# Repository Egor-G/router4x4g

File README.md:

4x M.2 LTE modems router project.
Based on Myirtech MYC-Y6ULX SoM.
Supply volatage 12-24V.
Openwrt OS.

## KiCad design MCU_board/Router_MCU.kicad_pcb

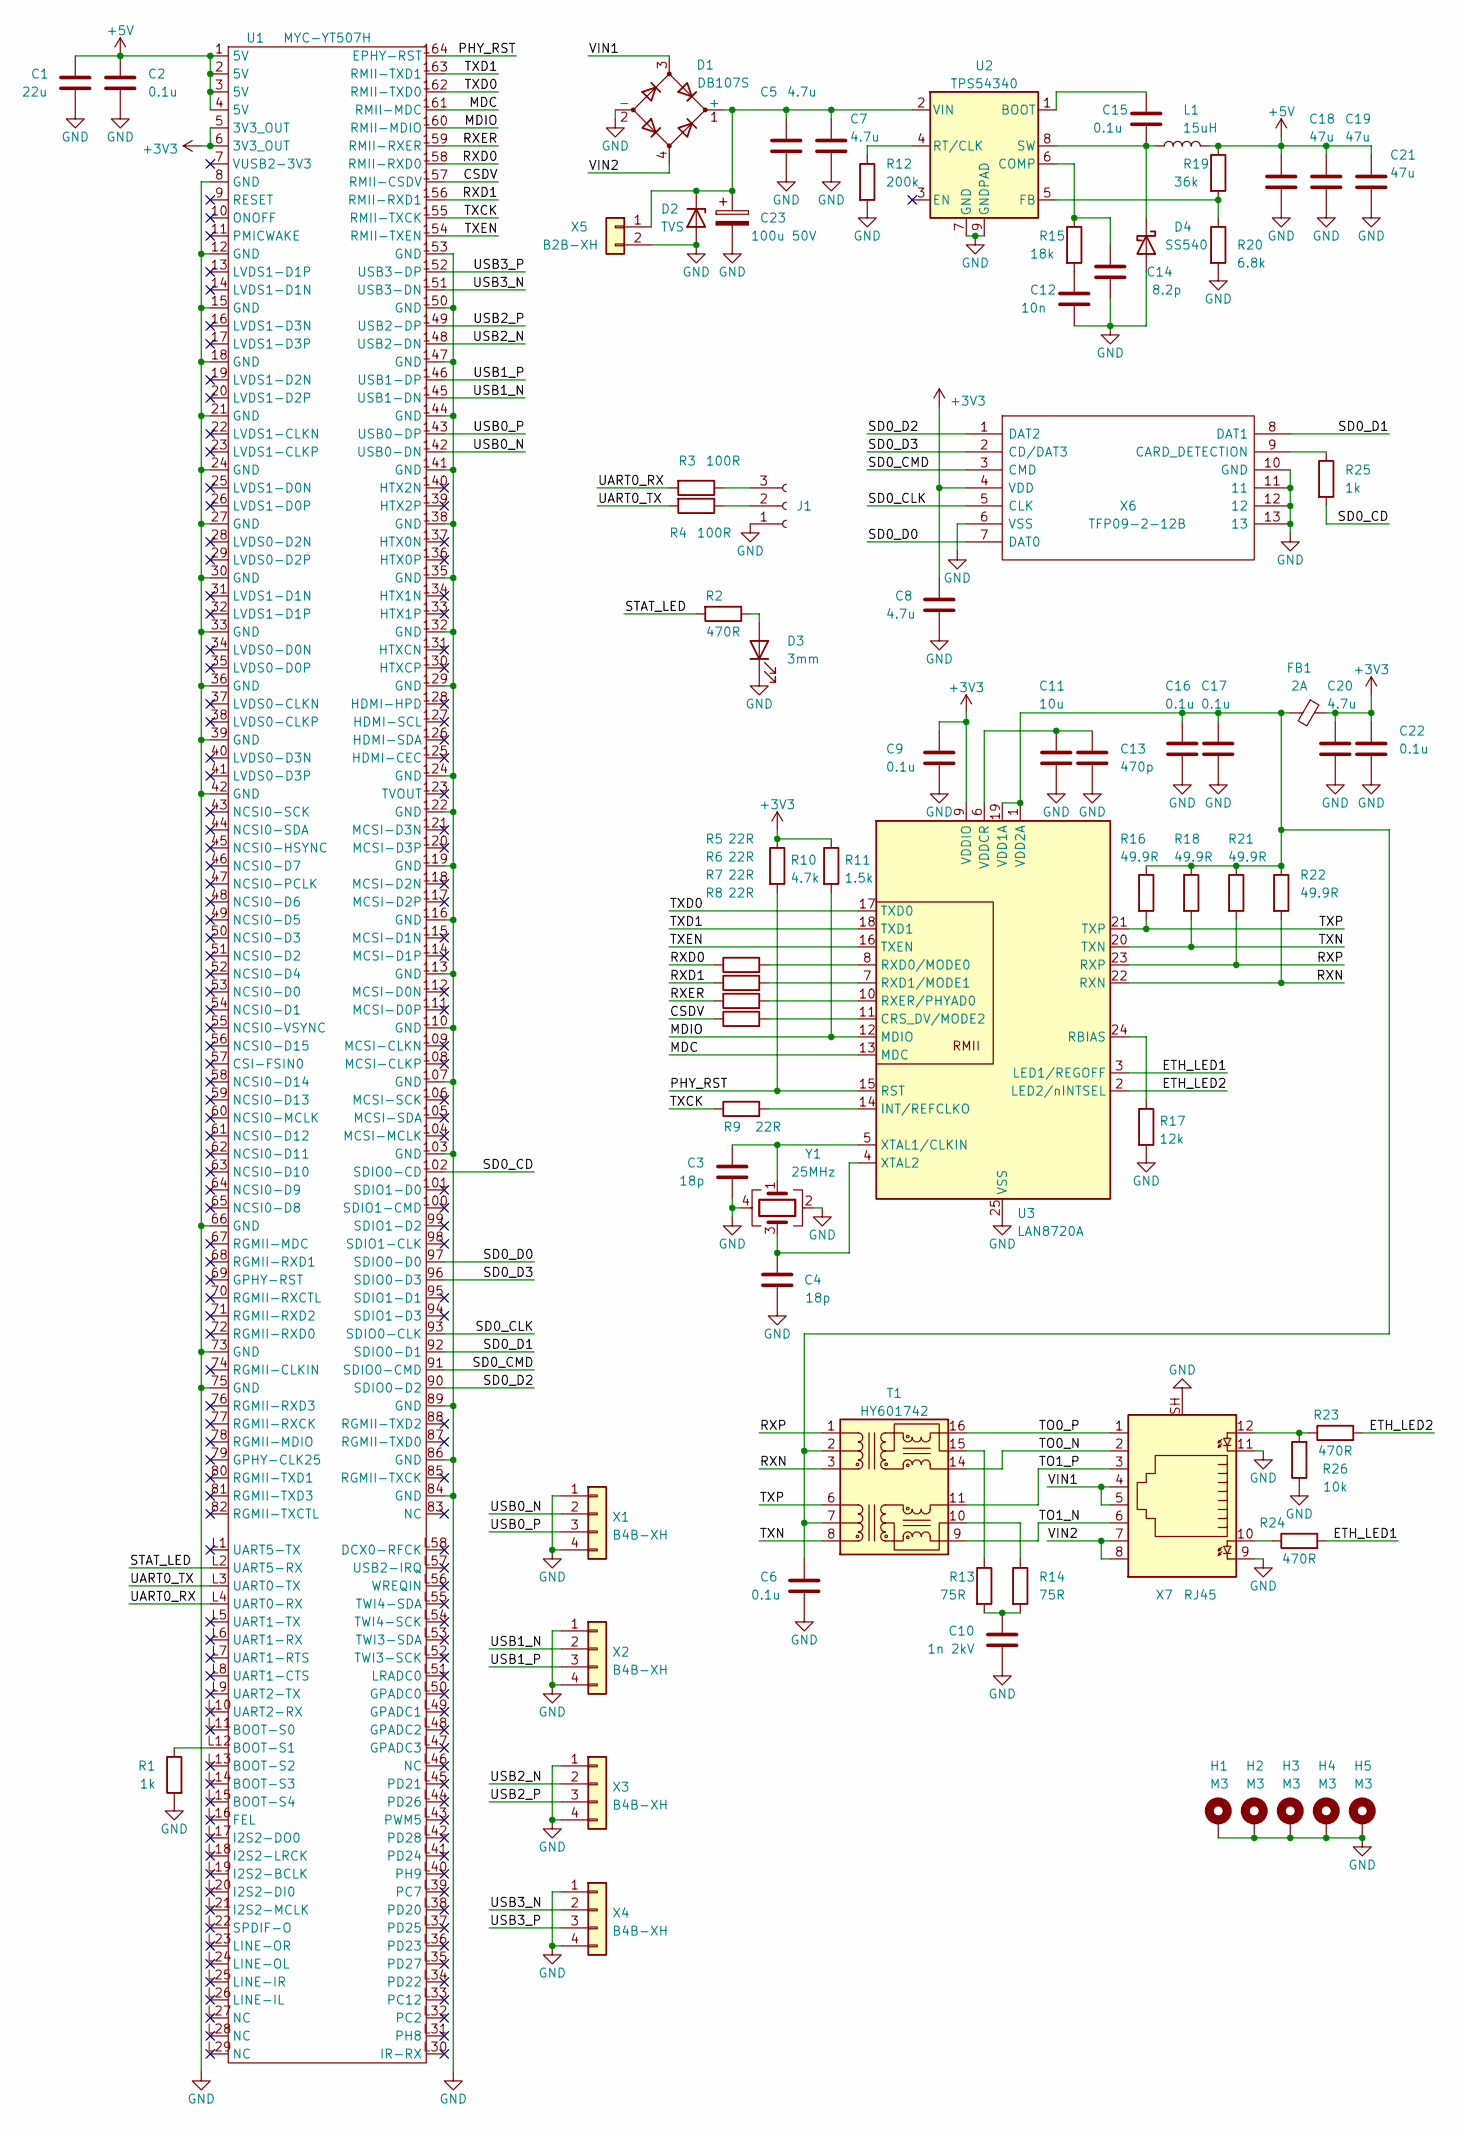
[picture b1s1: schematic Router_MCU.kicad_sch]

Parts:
C1: 22u; C_0805_2012Metric
C2, C6, C9, C15, C16, C17, C22: 0.1u; C_0603_1608Metric
C3, C4: 18p; C_0603_1608Metric
C5, C7: 4.7u; C_1206_3216Metric
C8, C20: 4.7u; C_0603_1608Metric
C10: 1n 2kV; C_1206_3216Metric
C11: 10u; C_0805_2012Metric
C12: 10n; C_0603_1608Metric
C13: 470p; C_0603_1608Metric
C14: 8.2p; C_0603_1608Metric
C18, C19, C21: 47u; C_1206_3216Metric
C23: 100u 50V; CP_Elec_10x10.5
D1: DB107S; Diode_Bridge_OnSemi_SDIP-4L
D2: TVS; D_SMA
D3: 3mm; LED_D3.0mm
D4: SS540; D_SMA
FB1: 2A; R_0805_2012Metric
H1, H2, H3, H4, H5: M3; MountingHole_3.5mm_Pad
J1: Header; PinHeader_1x03_P2.54mm_Vertical
L1: 15uH; L_Sunlord_MWSA1004S
R1, R25: 1k; R_0603_1608Metric
R2, R23, R24: 470R; R_0603_1608Metric
R3, R4: 100R; R_0603_1608Metric
R5, R6, R7, R8, R9: 22R; R_0603_1608Metric
R10: 4.7k; R_0603_1608Metric
R11: 1.5k; R_0603_1608Metric
R12: 200k; R_0603_1608Metric
R13, R14: 75R; R_0603_1608Metric
R15: 18k; R_0603_1608Metric
R16, R18, R21, R22: 49.9R; R_0603_1608Metric
R17: 12k; R_0603_1608Metric
R19: 36k; R_0603_1608Metric
R20: 6.8k; R_0603_1608Metric
R26: 10k; R_0603_1608Metric
T1: HY601742; Transformer_Ethernet_Bourns_PT61017PEL
U1: MYC-YT507H
U2: TPS54340; TI_SO-PowerPAD-8_ThermalVias
U3: LAN8720A; QFN-24-1EP_4x4mm_P0.5mm_EP2.6x2.6mm
X1, X2, X3, X4: B4B-XH; JST_XH_B4B-XH-A_1x04_P2.50mm_Vertical
X5: B2B-XH; JST_XH_B2B-XH-A_1x02_P2.50mm_Vertical
X6: TFP09-2-12B; TFP09212B; Manufacturer_Part_Number TFP09-2-12B
X7: RJ45; RJ45_Amphenol_RJHSE538X
Y1: 25MHz; Oscillator_SMD_Abracon_ASE-4Pin_3.2x2.5mm

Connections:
+3V3: C8.1, C9.1, C20.1, C22.1, FB1.1, R10.1, R11.1, U1.5 (3V3_OUT), U1.6 (3V3_OUT), U3.9 (VDDIO), X6.4 (VDD)
+5V: C1.1, C2.1, C18.1, C19.1, C21.1, L1.2, R19.1, U1.1 (5V), U1.2 (5V), U1.3 (5V), U1.4 (5V)
/CSDV: R8.1, U1.157 (RMII-CSDV)
/ETH_LED1: R24.2, U3.3 (LED1/REGOFF)
/ETH_LED2: R23.2, U3.2 (LED2/nINTSEL)
/MDC: U1.161 (RMII-MDC), U3.13 (MDC)
/MDIO: R11.2, U1.160 (RMII-MDIO), U3.12 (MDIO)
/PHY_RST: R10.2, U1.164 (EPHY-RST), U3.15 (RST)
/RXD0: R5.1, U1.158 (RMII-RXD0)
/RXD1: R6.1, U1.156 (RMII-RXD1)
/RXER: R7.1, U1.159 (RMII-RXER)
/RXN: R22.2, T1.3 (TD-), U3.22 (RXN)
/RXP: R21.2, T1.1 (TD+), U3.23 (RXP)
/SD0_CD: R25.2, U1.102 (SDIO0-CD)
/SD0_CLK: U1.93 (SDIO0-CLK), X6.5 (CLK)
/SD0_CMD: U1.91 (SDIO0-CMD), X6.3 (CMD)
/SD0_D0: U1.97 (SDIO0-D0), X6.7 (DAT0)
/SD0_D1: U1.92 (SDIO0-D1), X6.8 (DAT1)
/SD0_D2: U1.90 (SDIO0-D2), X6.1 (DAT2)
/SD0_D3: U1.96 (SDIO0-D3), X6.2 (CD/DAT3)
/STAT_LED: R2.2, U1.L2 (UART5-RX)
/TO0_N: T1.14 (TX-), X7.2
/TO0_P: T1.16 (TX+), X7.1
/TO1_N: T1.9 (RX-), X7.6
/TO1_P: T1.11 (RX+), X7.3
/TXCK: R9.1, U1.155 (RMII-TXCK)
/TXD0: U1.162 (RMII-TXD0), U3.17 (TXD0)
/TXD1: U1.163 (RMII-TXD1), U3.18 (TXD1)
/TXEN: U1.154 (RMII-TXEN), U3.16 (TXEN)
/TXN: R18.2, T1.8 (RD-), U3.20 (TXN)
/TXP: R16.2, T1.6 (RD+), U3.21 (TXP)
/UART0_RX: R3.2, U1.L4 (UART0-RX)
/UART0_TX: R4.2, U1.L3 (UART0-TX)
/USB0_N: U1.142 (USB0-DN), X1.2
/USB0_P: U1.143 (USB0-DP), X1.3
/USB1_N: U1.145 (USB1-DN), X2.2
/USB1_P: U1.146 (USB1-DP), X2.3
/USB2_N: U1.148 (USB2-DN), X3.2
/USB2_P: U1.149 (USB2-DP), X3.3
/USB3_N: U1.151 (USB3-DN), X4.2
/USB3_P: U1.152 (USB3-DP), X4.3
/VIN1: D1.3, X7.4, X7.5
/VIN2: D1.4, X7.7, X7.8
GND: C1.2, C2.2, C3.1, C4.1, C5.2, C6.2, C7.2, C8.2, C9.2, C10.1, C11.2, C12.2, C13.2, C14.1, C16.2, C17.2, C18.2, C19.2, C20.2, C21.2, C22.2, C23.2, D1.2 (-), D2.2 (A), D3.1 (K), D4.2 (A), H1.1, H2.1, H3.1, H4.1, H5.1, J1.1, R1.2, R12.2, R17.2, R20.2, R26.1, U1.8 (GND), U1.12 (GND), U1.15 (GND), U1.18 (GND), U1.21 (GND), U1.24 (GND), U1.27 (GND), U1.30 (GND), U1.33 (GND), U1.36 (GND), U1.39 (GND), U1.42 (GND), U1.66 (GND), U1.73 (GND), U1.75 (GND), U1.84 (GND), U1.86 (GND), U1.89 (GND), U1.103 (GND), U1.107 (GND), U1.110 (GND), U1.113 (GND), U1.116 (GND), U1.119 (GND), U1.122 (GND), U1.124 (GND), U1.129 (GND), U1.132 (GND), U1.135 (GND), U1.138 (GND), U1.141 (GND), U1.144 (GND), U1.147 (GND), U1.150 (GND), U1.153 (GND), U2.7 (GND), U2.9 (GNDPAD), U3.25 (VSS), X1.1, X1.4, X2.1, X2.4, X3.1, X3.4, X4.1, X4.4, X5.2, X6.6 (VSS), X6.10 (GND), X6.11, X6.12, X6.13, X7.9, X7.11, X7.SH, Y1.2, Y1.4
unnamed: C3.2, U3.5 (XTAL1/CLKIN), Y1.1
unnamed: C4.2, U3.4 (XTAL2), Y1.3
unnamed: C10.2, R13.2, R14.2
unnamed: C11.1, C13.1, U3.6 (VDDCR)
unnamed: C12.1, R15.2
unnamed: C14.2, R15.1, U2.6 (COMP)
unnamed: C15.1, U2.1 (BOOT)
unnamed: C15.2, D4.1 (K), L1.1, U2.8 (SW)
unnamed: C6.1, C16.1, C17.1, FB1.2, R16.1, R18.1, R21.1, R22.1, T1.2 (C_TD), T1.7 (C_RD), U3.1 (VDD2A), U3.19 (VDD1A)
unnamed: C5.1, C7.1, C23.1, D1.1 (+), D2.1 (K), U2.2 (VIN), X5.1
unnamed: D3.2 (A), R2.1
unnamed: J1.2, R4.1
unnamed: J1.3, R3.1
unnamed: R1.1, U1.L12 (BOOT-S1)
unnamed: R5.2, U3.8 (RXD0/MODE0)
unnamed: R6.2, U3.7 (RXD1/MODE1)
unnamed: R7.2, U3.10 (RXER/PHYAD0)
unnamed: R8.2, U3.11 (CRS_DV/MODE2)
unnamed: R9.2, U3.14 (INT/REFCLKO)
unnamed: R12.1, U2.4 (RT/CLK)
unnamed: R13.1, T1.15 (C_TX)
unnamed: R14.1, T1.10 (C_RX)
unnamed: R17.1, U3.24 (RBIAS)
unnamed: R19.2, R20.1, U2.5 (FB)
unnamed: R23.1, R26.2, X7.12
unnamed: R24.1, X7.10
unnamed: R25.1, X6.9 (CARD_DETECTION)

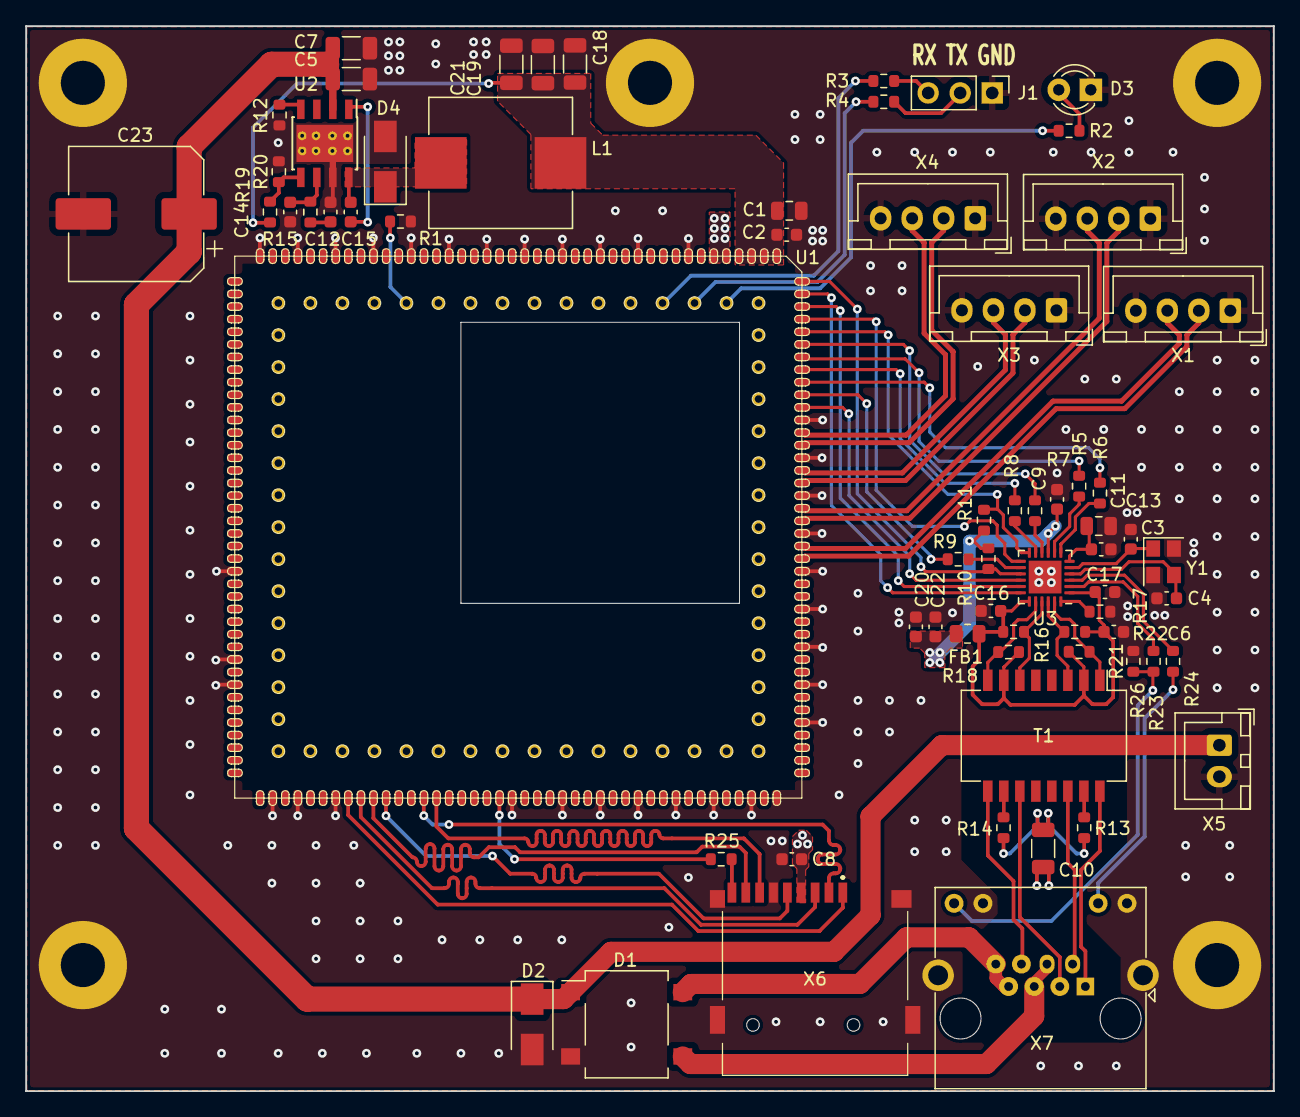
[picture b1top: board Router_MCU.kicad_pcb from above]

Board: 2 copper layers, 99.0 x 84.5 mm, 73 parts (0 on the bottom side), 71 nets.

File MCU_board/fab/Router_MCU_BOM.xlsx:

Designator | Comment | Footprint
C1, | 22u | 0805
C2, C6, C9, C15, C16, C17, C22, | 0.1u | 0603
C3, C4, | 18p | 0603
C5, C7, | 4.7u | 1206
C8, C20, | 4.7u | 0603
C10, | 1n 2kV | 1206
C11, | 10u | 0805
C12, | 10n | 0603
C13, | 470p | 0603
C14, | 8.2p | 0603
C18, C19, C21, | 47u | 1206
C23, | 100u 50V | 10x10.5
D1, | DB107S
D2, | TVS | SMA
D3, | 3mm
D4, | SS540 | SMA
FB1, | 2A | 0805
J1, | Header
L1, | 15uH
R1, R25, | 1k | 0603
R2, R23, R24, | 470R | 0603
R3, R4, | 100R | 0603
R5, R6, R7, R8, R9, | 22R | 0603
R10, | 4.7k | 0603
R11, | 1.5k | 0603
R12, | 200k | 0603
R13, R14, | 75R | 0603
R15, | 18k | 0603
R16, R18, R21, R22, | 49.9R | 0603
R17, | 12k | 0603
R19, | 36k | 0603
R20, | 6.8k | 0603
T1, | HY601742
U1, | MYC-YT507H
U2, | TPS54340 | SO-8
U3, | LAN8720A | QFN-24
X1, X2, X3, X4, | B4B-XH
X5, | B2B-XH
X6, | TFP09-2-12B
X7, | RJ45
Y1, | 25MHz | 3.2x2.5mm

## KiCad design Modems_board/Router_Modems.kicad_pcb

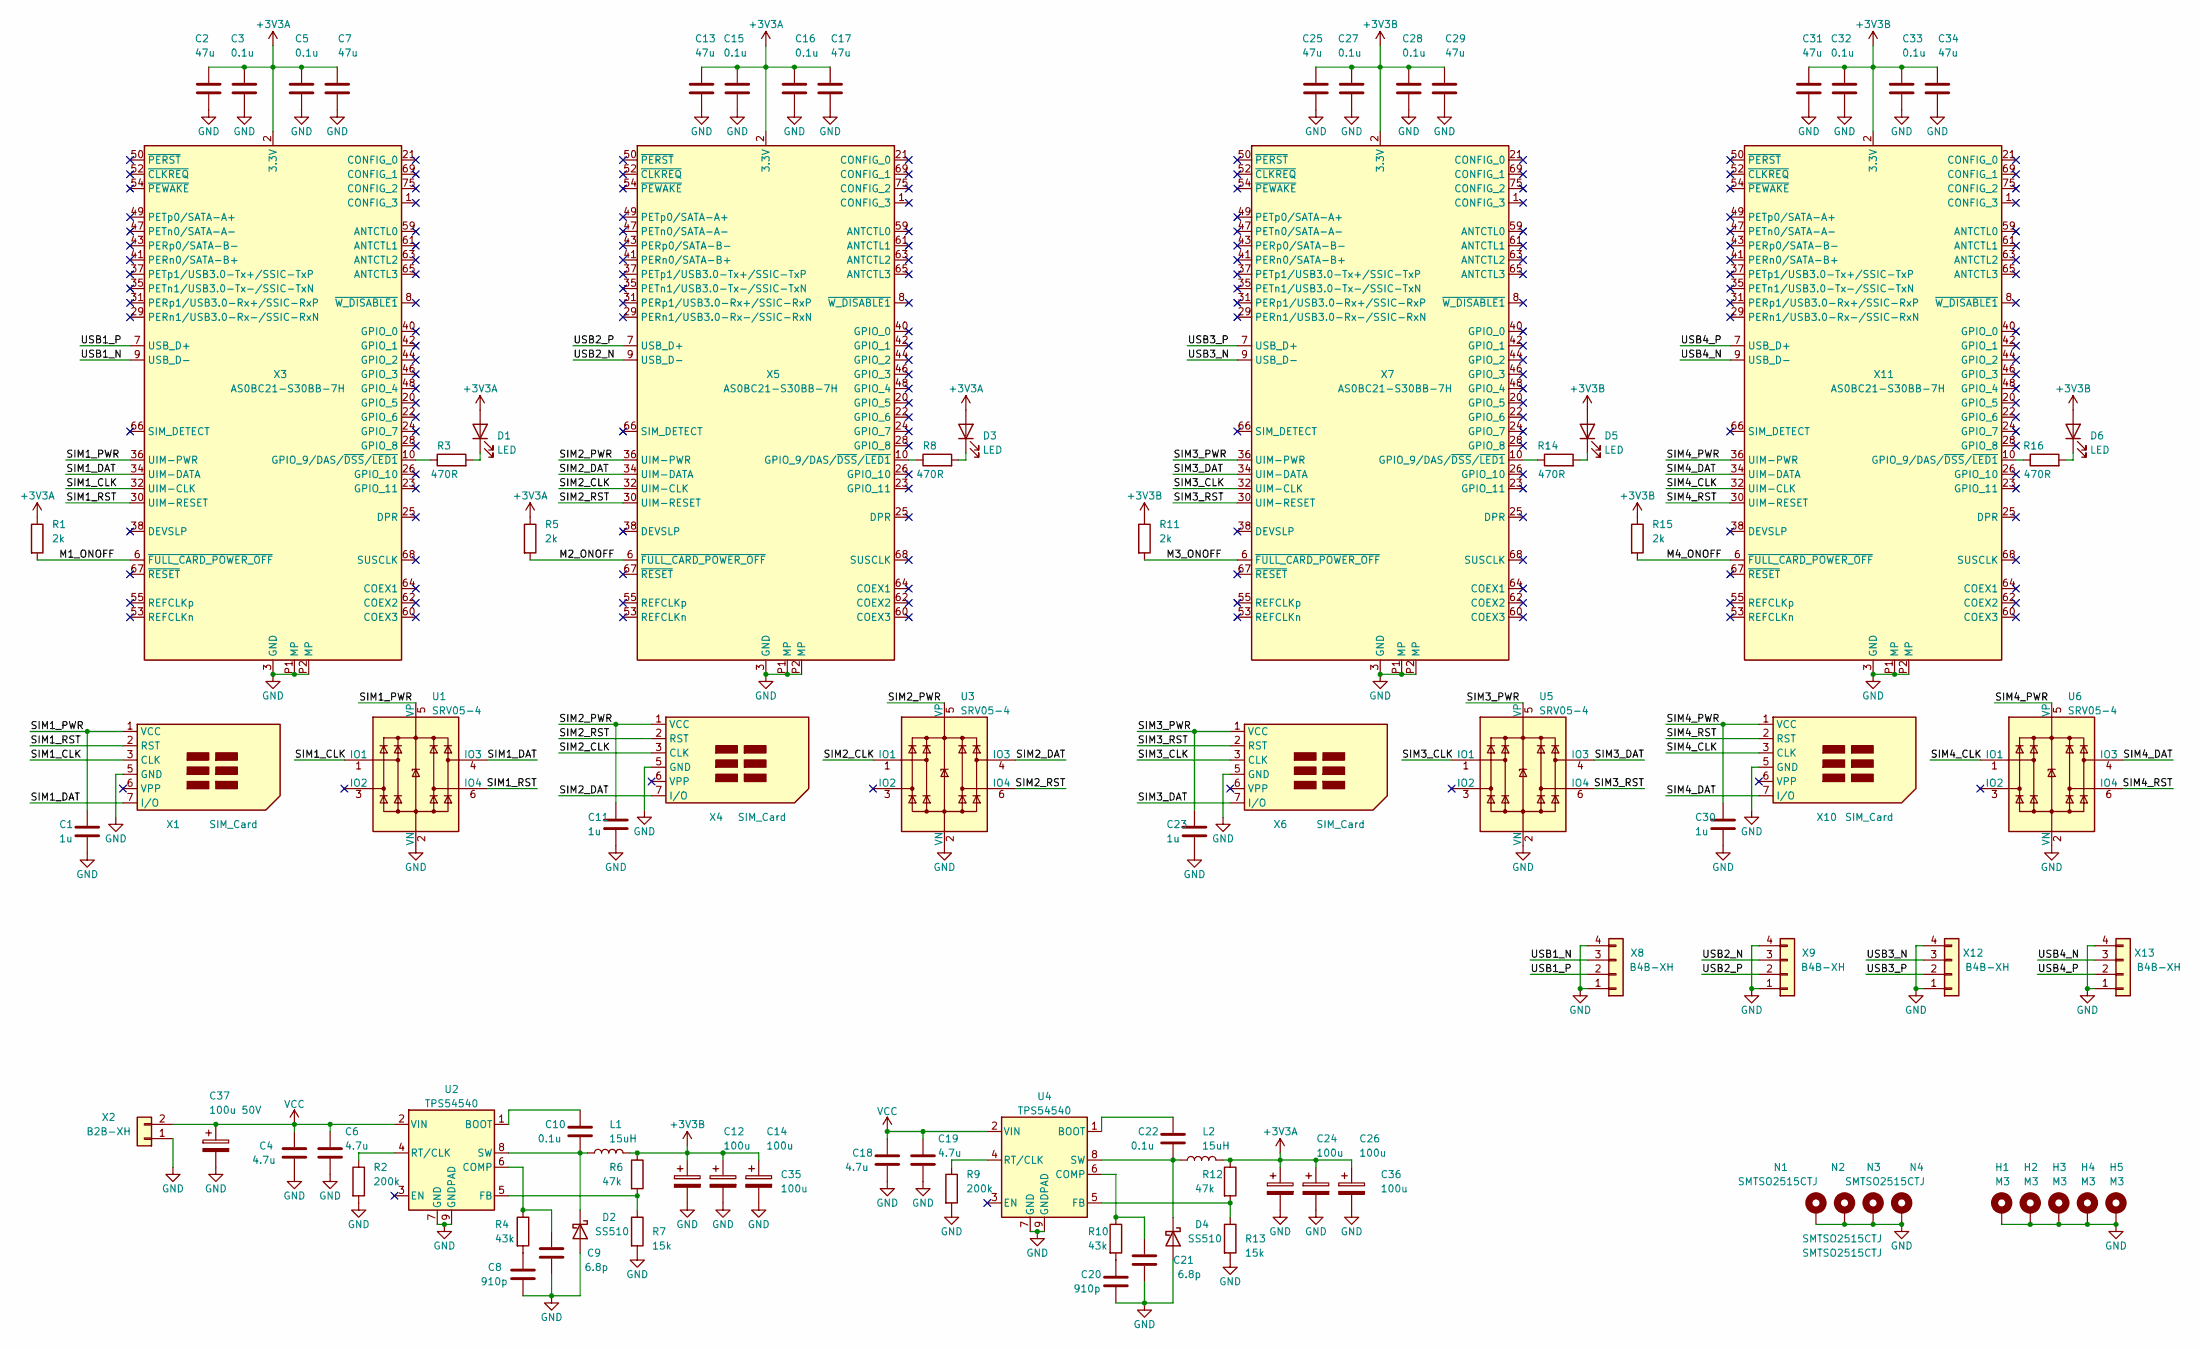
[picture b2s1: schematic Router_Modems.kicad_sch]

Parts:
C1, C11, C23, C30: 1u; C_0603_1608Metric
C2, C7, C13, C17, C25, C29, C31, C34: 47u; C_1206_3216Metric
C3, C5, C10, C15, C16, C22, C27, C28, C32, C33: 0.1u; C_0603_1608Metric
C4, C6, C18, C19: 4.7u; C_1206_3216Metric
C8, C20: 910p; C_0603_1608Metric
C9, C21: 6.8p; C_0603_1608Metric
C12, C14, C24, C26, C35, C36: 100u; CP_EIA-3528-15_AVX-H
C37: 100u 50V; CP_Elec_10x10.5
D1, D3, D5, D6: LED; LED_D3.0mm
D2, D4: SS510; D_SMA
H1, H2, H3, H4, H5: M3; MountingHole_3.5mm_Pad
L1, L2: 15uH; L_Sunlord_MWSA1004S
N1, N2, N3, N4: SMTSO2515CTJ; MountingHole_3.2mm_M3_Pad
R1, R5, R11, R15: 2k; R_0603_1608Metric
R2, R9: 200k; R_0603_1608Metric
R3, R8, R14, R16: 470R; R_0603_1608Metric
R4, R10: 43k; R_0603_1608Metric
R6, R12: 47k; R_0603_1608Metric
R7, R13: 15k; R_0603_1608Metric
U1, U3, U5, U6: SRV05-4; SOT-23-6
U2, U4: TPS54540; TI_SO-PowerPAD-8_ThermalVias
X1, X4, X6, X10: SIM_Card; FCI_7111S2015X02LF
X2: B2B-XH; JST_XH_B2B-XH-A_1x02_P2.50mm_Vertical
X3, X5, X7, X11: AS0BC21-S30BB-7H; AMPHENOL_MDT420B03001
X8, X9, X12, X13: B4B-XH; JST_XH_B4B-XH-A_1x04_P2.50mm_Vertical

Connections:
+3V3A: C2.1, C3.1, C5.1, C7.1, C13.1, C15.1, C16.1, C17.1, C24.1, C26.1, C36.1, D1.2 (A), D3.2 (A), L2.2, R1.1, R5.1, R12.1, X3.2 (3.3V), X3.4 (3.3V), X3.70 (3.3V), X3.72 (3.3V), X3.74 (3.3V), X5.2 (3.3V), X5.4 (3.3V), X5.70 (3.3V), X5.72 (3.3V), X5.74 (3.3V)
+3V3B: C12.1, C14.1, C25.1, C27.1, C28.1, C29.1, C31.1, C32.1, C33.1, C34.1, C35.1, D5.2 (A), D6.2 (A), L1.2, R6.1, R11.1, R15.1, X7.2 (3.3V), X7.4 (3.3V), X7.70 (3.3V), X7.72 (3.3V), X7.74 (3.3V), X11.2 (3.3V), X11.4 (3.3V), X11.70 (3.3V), X11.72 (3.3V), X11.74 (3.3V)
/M1_ONOFF: R1.2, X3.6 (~FULL_CARD_POWER_OFF)
/M2_ONOFF: R5.2, X5.6 (~FULL_CARD_POWER_OFF)
/M3_ONOFF: R11.2, X7.6 (~FULL_CARD_POWER_OFF)
/M4_ONOFF: R15.2, X11.6 (~FULL_CARD_POWER_OFF)
/SIM1_CLK: U1.1 (IO1), X1.3 (CLK), X3.32 (UIM-CLK)
/SIM1_DAT: U1.4 (IO3), X1.7 (I/O), X3.34 (UIM-DATA)
/SIM1_PWR: C1.1, U1.5 (VP), X1.1 (VCC), X3.36 (UIM-PWR)
/SIM1_RST: U1.6 (IO4), X1.2 (RST), X3.30 (UIM-RESET)
/SIM2_CLK: U3.1 (IO1), X4.3 (CLK), X5.32 (UIM-CLK)
/SIM2_DAT: U3.4 (IO3), X4.7 (I/O), X5.34 (UIM-DATA)
/SIM2_PWR: C11.1, U3.5 (VP), X4.1 (VCC), X5.36 (UIM-PWR)
/SIM2_RST: U3.6 (IO4), X4.2 (RST), X5.30 (UIM-RESET)
/SIM3_CLK: U5.1 (IO1), X6.3 (CLK), X7.32 (UIM-CLK)
/SIM3_DAT: U5.4 (IO3), X6.7 (I/O), X7.34 (UIM-DATA)
/SIM3_PWR: C23.1, U5.5 (VP), X6.1 (VCC), X7.36 (UIM-PWR)
/SIM3_RST: U5.6 (IO4), X6.2 (RST), X7.30 (UIM-RESET)
/SIM4_CLK: U6.1 (IO1), X10.3 (CLK), X11.32 (UIM-CLK)
/SIM4_DAT: U6.4 (IO3), X10.7 (I/O), X11.34 (UIM-DATA)
/SIM4_PWR: C30.1, U6.5 (VP), X10.1 (VCC), X11.36 (UIM-PWR)
/SIM4_RST: U6.6 (IO4), X10.2 (RST), X11.30 (UIM-RESET)
/USB1_N: X3.9 (USB_D-), X8.3
/USB1_P: X3.7 (USB_D+), X8.2
/USB2_N: X5.9 (USB_D-), X9.3
/USB2_P: X5.7 (USB_D+), X9.2
/USB3_N: X7.9 (USB_D-), X12.3
/USB3_P: X7.7 (USB_D+), X12.2
/USB4_N: X11.9 (USB_D-), X13.3
/USB4_P: X11.7 (USB_D+), X13.2
GND: C1.2, C2.2, C3.2, C4.2, C5.2, C6.2, C7.2, C8.2, C9.1, C11.2, C12.2, C13.2, C14.2, C15.2, C16.2, C17.2, C18.2, C19.2, C20.2, C21.1, C23.2, C24.2, C25.2, C26.2, C27.2, C28.2, C29.2, C30.2, C31.2, C32.2, C33.2, C34.2, C35.2, C36.2, C37.2, D2.2 (A), D4.2 (A), H1.1, H2.1, H3.1, H4.1, H5.1, N1.1, N2.1, N3.1, N4.1, R2.2, R7.2, R9.2, R13.2, U1.2 (VN), U2.7 (GND), U2.9 (GNDPAD), U3.2 (VN), U4.7 (GND), U4.9 (GNDPAD), U5.2 (VN), U6.2 (VN), X1.5 (GND), X2.1, X3.3 (GND), X3.5 (GND), X3.11 (GND), X3.27 (GND), X3.33 (GND), X3.39 (GND), X3.45 (GND), X3.51 (GND), X3.57 (GND), X3.71 (GND), X3.73 (GND), X3.P1 (MP), X3.P2 (MP), X4.5 (GND), X5.3 (GND), X5.5 (GND), X5.11 (GND), X5.27 (GND), X5.33 (GND), X5.39 (GND), X5.45 (GND), X5.51 (GND), X5.57 (GND), X5.71 (GND), X5.73 (GND), X5.P1 (MP), X5.P2 (MP), X6.5 (GND), X7.3 (GND), X7.5 (GND), X7.11 (GND), X7.27 (GND), X7.33 (GND), X7.39 (GND), X7.45 (GND), X7.51 (GND), X7.57 (GND), X7.71 (GND), X7.73 (GND), X7.P1 (MP), X7.P2 (MP), X8.1, X8.4, X9.1, X9.4, X10.5 (GND), X11.3 (GND), X11.5 (GND), X11.11 (GND), X11.27 (GND), X11.33 (GND), X11.39 (GND), X11.45 (GND), X11.51 (GND), X11.57 (GND), X11.71 (GND), X11.73 (GND), X11.P1 (MP), X11.P2 (MP), X12.1, X12.4, X13.1, X13.4
unnamed: C8.1, R4.2
unnamed: C9.2, R4.1, U2.6 (COMP)
unnamed: C10.1, U2.1 (BOOT)
unnamed: C10.2, D2.1 (K), L1.1, U2.8 (SW)
unnamed: C20.1, R10.2
unnamed: C21.2, R10.1, U4.6 (COMP)
unnamed: C22.1, U4.1 (BOOT)
unnamed: C22.2, D4.1 (K), L2.1, U4.8 (SW)
unnamed: D1.1 (K), R3.2
unnamed: D3.1 (K), R8.2
unnamed: D5.1 (K), R14.2
unnamed: D6.1 (K), R16.2
unnamed: R2.1, U2.4 (RT/CLK)
unnamed: R3.1, X3.10 (GPIO_9/DAS/~DSS/~LED1)
unnamed: R6.2, R7.1, U2.5 (FB)
unnamed: R8.1, X5.10 (GPIO_9/DAS/~DSS/~LED1)
unnamed: R9.1, U4.4 (RT/CLK)
unnamed: R12.2, R13.1, U4.5 (FB)
unnamed: R14.1, X7.10 (GPIO_9/DAS/~DSS/~LED1)
unnamed: R16.1, X11.10 (GPIO_9/DAS/~DSS/~LED1)
VCC: C4.1, C6.1, C18.1, C19.1, C37.1, U2.2 (VIN), U4.2 (VIN), X2.2

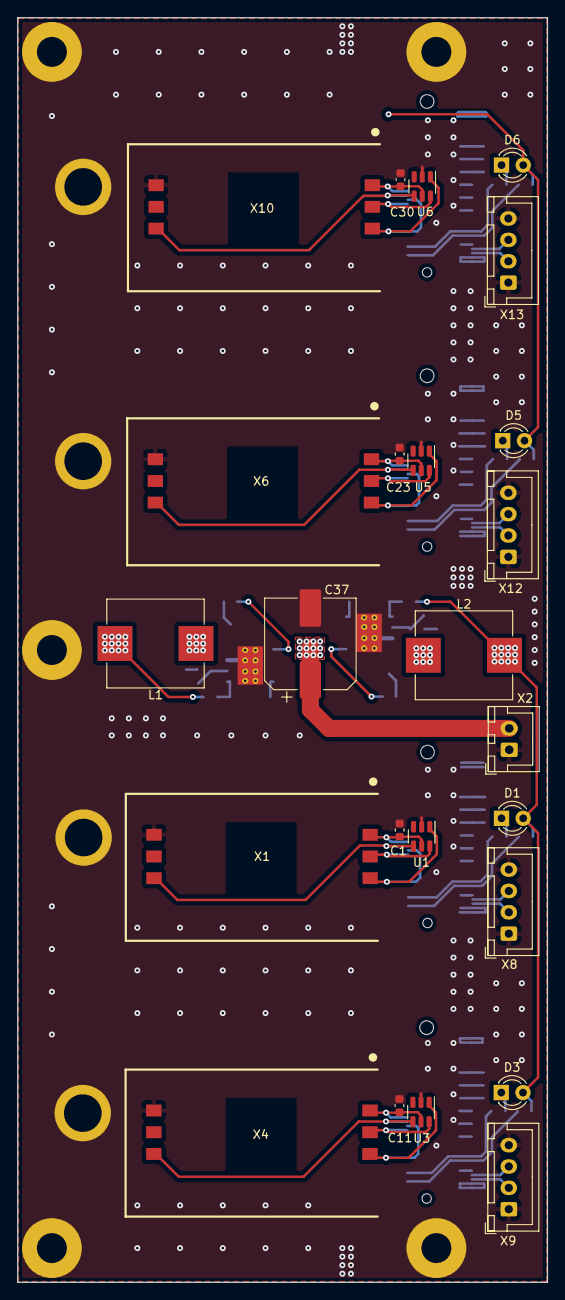
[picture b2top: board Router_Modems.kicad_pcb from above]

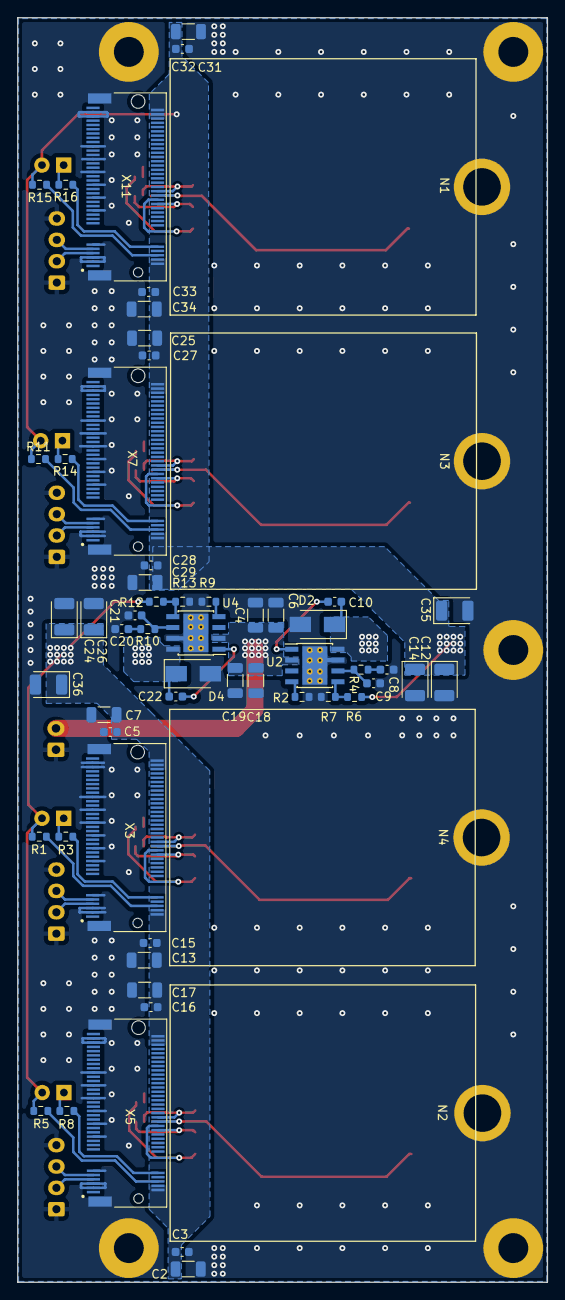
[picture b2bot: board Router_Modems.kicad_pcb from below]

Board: 2 copper layers, 62.0 x 148.0 mm, 89 parts (60 on the bottom side), 52 nets.

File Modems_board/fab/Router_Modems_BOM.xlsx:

Designator | Comment | Footprint
C1, C11, C23, C30, | 1u | 0603
C2, C7, C13, C17, C25, C29, C31, C34, | 47u | 1206
C3, C5, C10, C15, C16, C22, C27, C28, C32, C33, | 0.1u | 0603
C4, C6, C18, C19, | 4.7u | 1206
C8, C20, | 910p | 0603
C9, C21, | 6.8p | 0603
C12, C14, C24, C26, C35, C36, | 100u | 3528
C37, | 100u 50V | 10x10.5
D1, D3, D5, D6, | LED
D2, D4, | SS510 | SMA
L1, L2, | 15uH
N1, N2, N3, N4, | SMTSO2515CTJ
R1, R5, R11, R15, | 2k | 0603
R2, R9, | 200k | 0603
R3, R8, R14, R16, | 470R | 0603
R4, R10, | 43k | 0603
R6, R12, | 47k | 0603
R7, R13, | 15k | 0603
U1, U3, U5, U6, | SRV05-4 | SOT-23-6
U2, U4, | TPS54540 | SO-8
X1, X4, X6, X10, | 7111S2015X02LF
X2, | B2B-XH
X3, X5, X7, X11, | AS0BC21-S30BB-7H
X8, X9, X12, X13, | B4B-XH

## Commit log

2022-09-11 initial
2022-12-26 Move to YT507 module, split boards
2023-02-11 routing procs
2023-02-14 Modems board ready
2023-02-15 mcu_pdb_routing
2023-02-15 Ready for order
2023-03-09 remove modems gpio ctrls
2023-03-17 lan8720 led config resistor
